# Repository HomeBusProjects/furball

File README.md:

# The Furball

Furball is an open-source hardware project intended to help with the research and development of [Homebus](https://github.com/HomeBusProjects), an IoT auto-provisioning framework and data processing network built on top of MQTT. Note that Homebus is not even alpha quality software at this time and is still undergoing architectural changes and development.

The name 'Furball' is an homage to Dave Mills' ["Fuzzball"](https://en.wikipedia.org/wiki/Fuzzball_router), one of the first routers on the nascent Internet.

The Furball hardware performs environmental monitoring and is intended to be deployed indoors with fixed power source. It will auto-provision with Homebus to feed sensor readings into an IoT system.

## Hardware

Furball is based on the ESP32 processor. ESP32 is more capable than its predecessor, the ESP8266 while remaining inexpensive. The ESP32 supports both 802.11b/g/n Wifi and Bluetooth 4.2/BLE. It also has hardware acceleration for encryption. It includes 4 SPI controllers, 2 I2C controllers, 3 UARTs, up to 18 channels of ADC and two 8 bit DACs. You'll never use all of those at once as it doesn't have enough GPIO pins to express all of those functions, though you can map many of the hardware controllers to particular GPIO pins.

The hardware supports several environmental sensors:
- temperature
- humidity
- air pressure 
- light intensity
- occupancy 
- sound intensity
- volatile organics

It's powered via USB. The hardware currently uses a LOLIN32 board which has a JST connector for a LiPo battery. The software is currently in no way optimized for battery operation.

The hardware also includes either a tri-color LED or RGB LED with controller.

While the Furball hardware is designed to work with the Furball software, it should also work with other software like [ESPEasy32](https://www.letscontrolit.com/wiki/index.php?title=ESPEasy32), [ESPHome](https://esphome.io/) or custom software.

See the [Furball Hardware Guide](HARDWARE.md) for assembly instructions.

### Temperature, Humidity and Pressure

Furball currently uses the [BME280](https://www.bosch-sensortec.com/products/environmental-sensors/humidity-sensors-bme280/) - temperature/pressure/humidity sensor, $2.57 in single unit quantities, AliExpress, or the [BME680](https://www.bosch-sensortec.com/products/environmental-sensors/gas-sensors-bme680/) - temperature/pressure/humidity/VOC sensor, $9.92 in single unit quanitties on AliExpress.

### Occupancy

Furball hardware has a 3 pin header for a [PIR](https://en.wikipedia.org/wiki/Passive_infrared_sensor) sensor.

### Sound Pressure

Furball hardware currently uses a small amplified microphone on a breakout board, compatible with [Sparkfun's Sound Detector](https://www.sparkfun.com/products/12642).

### Light

Furball uses the [TSL2561](https://ams.com/tsl2561)  Digital Luminosity sensor - $1 in single unit quantities, AliExpress.

### VOC

Furball uses the BME680, which is a BME280 plus a VOC sensor. If you're building a Furball which can read VOCs, you only need the BME680 and not the BME280.

(note: I originally used a [CCS811](https://ams.com/ccs811) but had a lot of problems with cheaper units. It also doesn't truly measure CO2 but infers it from the VOC reading.)

### Total Cost

If bought through AliExpress, parts cost should run roughly:
- $6 - ESP32 LOLIN32
- $2.57 - BME280
- $1 - TSL2561
- $9 - BME680
- $1 - random resistors, capacitors, tri-color LED

Total of roughly $20 in parts before the circuit board.

## Optional Hardware

### Particle sensor

Furball has an optional port to connect a Plantower [PMS5003](http://www.plantower.com/en/content/?108.html) particle sensor. The particle sensor allows you to monitor air quality.

## Software

Furball's software is built on the Arduino Core using [PlatformIO](https://platformio.org/) as its build system. I prefer PlatformIO because it's fast, has a good library manager, lets you build for arbitrary platforms without having to manually install support for them, and lets you use your editor of choice.

Create a `src/config.h` file based on `src/config.h-example` and configure Wifi and the MQTT broker.

Once you've installed PlatformIO you can build the Furball firmware by running:
```
platformio run
```

in its top level directory.

To flash the firmware, run:
```
platformio run -t upload
```

It currently supports OTA updates.

## Iterations

The intial version is a simple breadboard.

Second version is a soldered printed circuit breadboard.

The third and current version will be a custom printed circuit board with modules soldered into it.

A hypothetical fourth version would be a custom printed circuit board with surface mount components and will have components mounted directly on it rather than using 3rd party modules.

# License

Software and documentation is licensed under the [MIT license](https://romkey.mit-license.org/).

Circuits are licensed under [Creative Commons Attribution Share-Alike license](https://creativecommons.org/licenses/by-sa/4.0).

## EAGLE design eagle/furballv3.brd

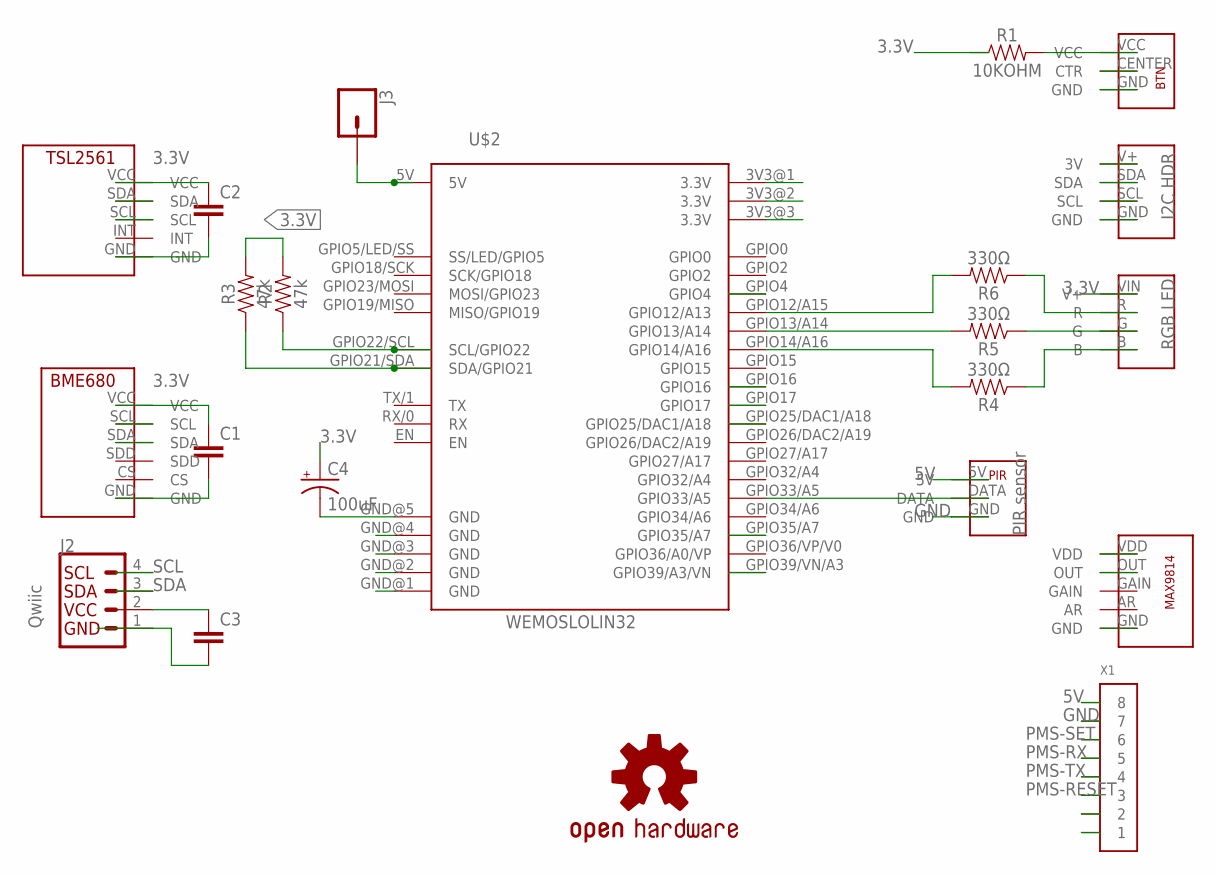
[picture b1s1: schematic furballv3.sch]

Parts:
C1, C2, C3: 10pF; CAP-PTH-SMALL2
C4: 100uF; CPOL-RADIAL-2.5MM-6.5MM
J2: QWIIC_CONNECTORJS-1MM; 1X04_1MM_RA
J3: CONN_01; 1X01
LOGO1: OSHW-LOGOL; OSHW-LOGO-L
R1: 10KOHM; AXIAL-0.3-KIT
R2, R3: 47k; AXIAL-0.3
R4, R5, R6: 330Ω; AXIAL-0.3
U$1: PIRHEADER
U$2: WEMOSLOLIN32; LOLIN32VAR1
U$3: BME680BREAKOUT
U$4: TSL2561BREAKOUT
U$5: RGBLEDHEADER; RGBLEDHDR
U$6: I2CHEADER
U$7: MAX9814BREAKOUT
U$8: PUSHBUTTONHEADER
X1: CONN_8-1-53261; PB-53261-08

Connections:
3.3V: C1.1, C2.1, C3.1, C4.1 (+), J2.2 (VCC), R1.P$1 (1), R2.P$2 (2), R3.P$2 (2), U$2.3V3@1 (3.3V), U$2.3V3@2 (3.3V), U$2.3V3@3 (3.3V), U$3.VCC, U$4.VCC, U$5.VIN (V+), U$6.V+ (3V), U$7.VDD
5V: J3.1, U$1.5V, U$2.5V, X1.8
BUTTON: U$2.GPIO35/A7, U$8.CENTER (CTR)
GND: C1.2, C2.2, C3.2, C4.2 (-), J2.1 (GND), U$1.GND, U$2.GND@1 (GND), U$2.GND@2 (GND), U$2.GND@3 (GND), U$2.GND@4 (GND), U$2.GND@5 (GND), U$3.GND, U$4.GND, U$6.GND, U$7.GND, U$8.GND, X1.7
unnamed: R5.P$1 (1), U$5.G
unnamed: R6.P$2 (2), U$2.GPIO12/A15 (GPIO12/A13)
unnamed: U$1.DATA, U$2.GPIO33/A5
unnamed: R5.P$2 (2), U$2.GPIO13/A14
unnamed: R4.P$2 (2), U$2.GPIO14/A16
unnamed: R4.P$1 (1), U$5.B
unnamed: R6.P$1 (1), U$5.R
unnamed: R1.P$2 (2), U$8.VCC
PMS-RESET: U$2.GPIO25/DAC1/A18, X1.3
PMS-RX: U$2.GPIO16, X1.5
PMS-SET: U$2.GPIO4, X1.6
PMS-TX: U$2.GPIO17, X1.4
SCL: J2.4 (SCL), R2.P$1 (1), U$2.GPIO22/SCL (SCL/GPIO22), U$3.SCL, U$4.SCL, U$6.SCL
SDA: J2.3 (SDA), R3.P$1 (1), U$2.GPIO21/SDA (SDA/GPIO21), U$3.SDA, U$4.SDA, U$6.SDA
SOUND: U$2.GPIO39/VN/A3 (GPIO39/A3/VN), U$7.OUT

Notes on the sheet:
Qwiic
PIR sensor
RGB LED
I2C HDR

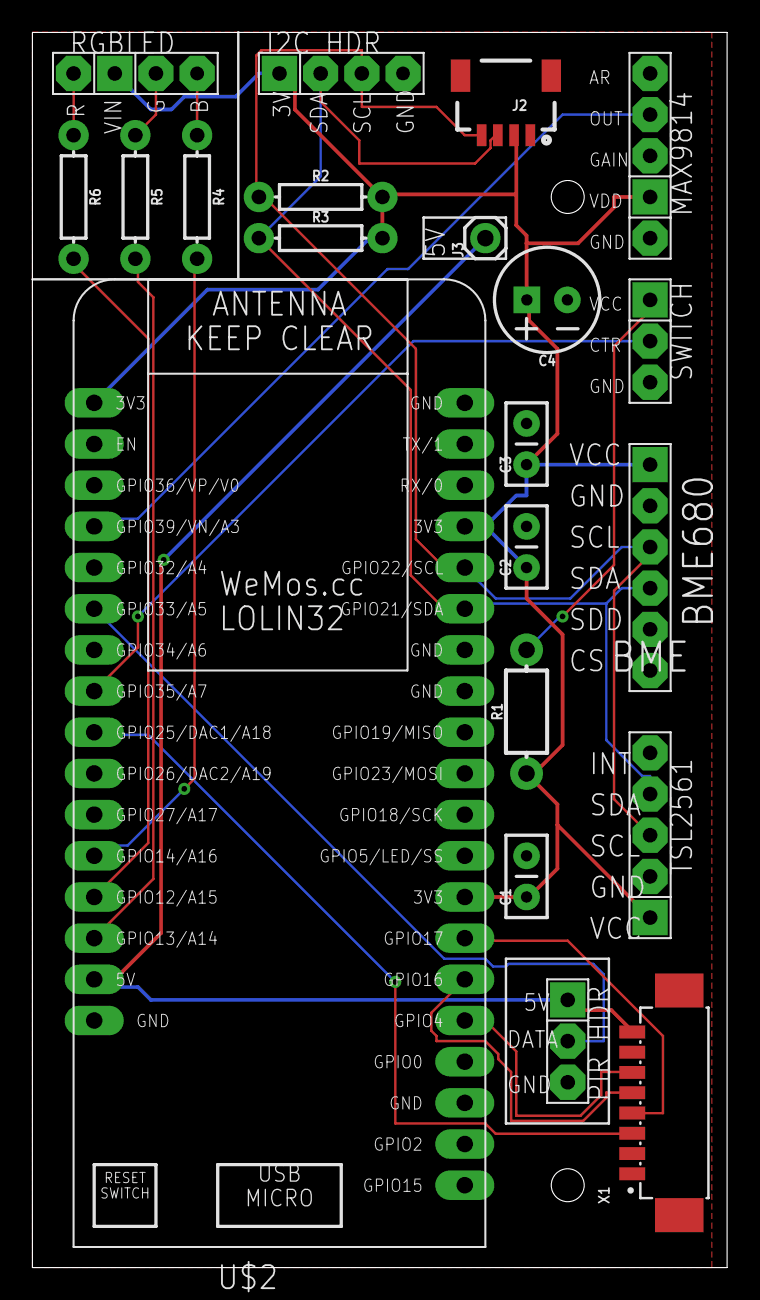
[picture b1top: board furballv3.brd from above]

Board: 2 copper layers, 42.9 x 76.2 mm, 22 parts (1 on the bottom side), 19 nets.

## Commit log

2018-07-13 initial checkin
2018-07-15 Hello World!
2018-08-21 added REST API support
    many sensor updates
2018-11-28 rewrote lib_deps properly
2019-05-04 added Eagle schematics and some hardware documentation
    clean up unused drivers
    clean up path through main
    clean up JSON
2019-05-04 cleaned up debug messages
2019-05-04 missed a couple of debug messages
2019-05-04 updates to README
2019-05-04 added pictures showing parts and values
2019-05-04 try to fix markdown
2019-05-05 updated hardware doc
    updated config.h example
2019-05-08 switch to PubSubClient, drop Adafruit IO support
    publish UUID in JSON
2019-05-11 include IP address and RSSI in updates
2019-05-20 start updating sooner after boot
    added preliminary support for sound levels
2019-05-30 testing different PMS5003 driver
    new script to report build info
    PlatformIO build options changed to include build info
    system attribute now includes build info
2019-06-19 experiment in squaring sound levels
2019-06-22 add BME680 library to platformio.ini
    tune BM280 and BME680 configurations to indoor use cases
    get temperature, humidity and pressure as floats, report with 1 decimal place of precision
2019-06-28 sanity check PMS5003 values before uploading them
2019-06-28 updated config.h-example
2019-07-06 clean up platformio.ini
    start to use a HomeBus endpoint for publishing to MQTT
    sound level sensor should always use 32 bit values
2019-07-19 s/ESP.h/Esp.h/
2019-07-19 removed unused sensor
2019-07-19 added .pio to .gitignore for PlatformIO 4
2019-07-28 cleanup platformio.ini
    make pubsubclient available outside of main
    cleanup/clarify sound sensor code
2019-08-03 moved sensors into their own directory
    eliminated JC_Button and IFTTTWebhook
2019-09-02 led indicator
2019-09-03 refactored to work with multiball-library
2019-10-20 added FastLED for indicator
    reactored for MultiballApp
    fixed obscure argument order issue for Led
2020-01-06 rewritten to use multiball homebus code
2020-02-01 more README updates
2020-03-07 stuff
2020-03-07 new config.h file Travis CI builds
    cp config.h file before build
2020-05-22 Travis support
2020-05-22 index on master: d320d10 more README updates
2020-05-27 added diagnostics code (eventually to be split out into a library)
2020-05-27 added Travis badge
2020-06-01 added upload script
2020-06-26 change id to source
2020-06-26 get rid of indicator
    make platformio do a deep scan of dependencies (fixes missing Ticker.h problem)
2020-06-27 set time with NTP
    include timestamp in updates
2020-06-27 added is_present() support for sensors
    only update sensor readings if the sensor is present
2020-06-27 new ADSL1115 ADC support
2020-06-27 fix Travis
2020-07-06 moved diagnostics into a separate library
2024-04-15 added esphome definition

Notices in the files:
parts and their libraries:
SparkFun-Connectors: Licensing: Creative Commons ShareAlike 4.0 International - https://creativecommons.org/licenses/by-sa/4.0
